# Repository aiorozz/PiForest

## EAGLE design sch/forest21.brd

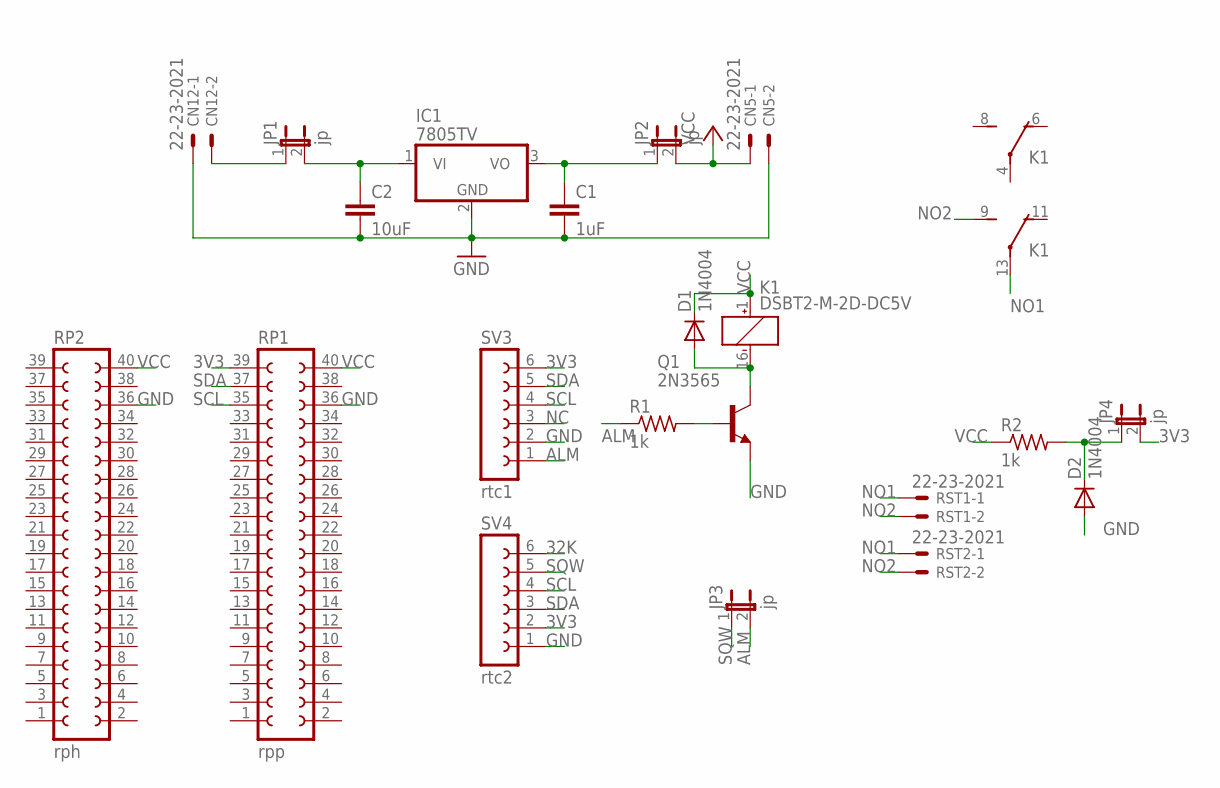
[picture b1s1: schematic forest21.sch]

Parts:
C1: 1uF; C025-030X050
C2: 10uF; C025-030X050
CN5, CN12: 22-23-2021
D1, D2: 1N4004; DO41-10
IC1: 7805TV; TO220V
JP1, JP2, JP3, JP4: jp; JP1
K1: DSBT2-M-2D-DC5V; DS-BT
Q1: 2N3565; TO92
R1, R2: 1k; 0207/7
RP1: rpp; FE20-2
RP2: rph; FE20-2
RST1, RST2: 22-23-2021
SV3: rtc1; FE06
SV4: rtc2; FE06

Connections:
3V3: JP4.2, RP1.39, SV3.6, SV4.2
32K: SV4.6
ALM: JP3.2, R1.1, SV3.1
GND: C1.2, C2.2, CN5.2, CN12.1, D2.A, IC1.2 (GND), Q1.3 (E), RP1.36, RP2.36, SV3.2, SV4.1
unnamed: CN12.2, JP1.1
unnamed: C2.1, IC1.1 (VI), JP1.2
unnamed: C1.1, IC1.3 (VO), JP2.1
unnamed: Q1.2 (B), R1.2
unnamed: D1.A, K1.16 (-), Q1.1 (C)
unnamed: D2.C, JP4.1, R2.2
NC: SV3.3
NO1: K1.13, RST1.1, RST2.1
NO2: K1.9 (S), RST1.2, RST2.2
SCL: RP1.35, SV3.4, SV4.4
SDA: RP1.37, SV3.5, SV4.3
SQW: JP3.1, SV4.5
VCC: CN5.1, D1.C, JP2.2, K1.1 (+), R2.1, RP1.40, RP2.40

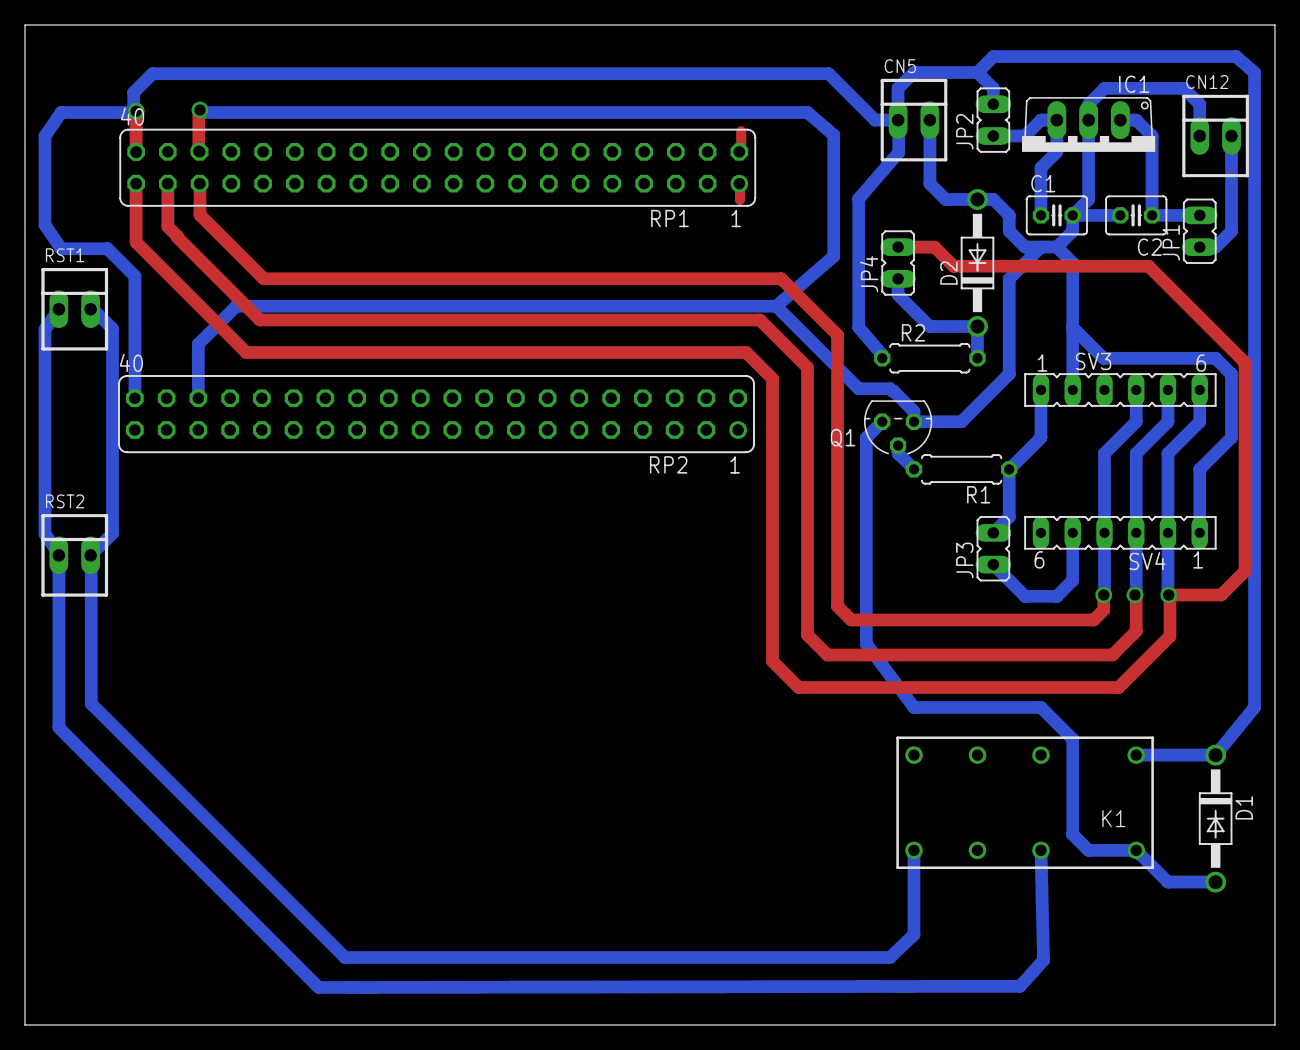
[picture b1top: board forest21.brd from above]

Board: 2 copper layers, 100.0 x 80.0 mm, 21 parts (0 on the bottom side), 15 nets.

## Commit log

2017-09-07 Source code for Forest
2017-09-07 Schematics for PCB Boards
2017-09-07 Actions PSP
2017-09-07 Code to the base Vignette in phenopix (R)
2017-09-07 Other functions
2017-09-07 Update Spatial
2017-09-07 Script to Exif WB action
    Script to Exif WB PSP action
2017-09-08 updated exif
2017-09-10 update to extract rdn gdn bdn values
